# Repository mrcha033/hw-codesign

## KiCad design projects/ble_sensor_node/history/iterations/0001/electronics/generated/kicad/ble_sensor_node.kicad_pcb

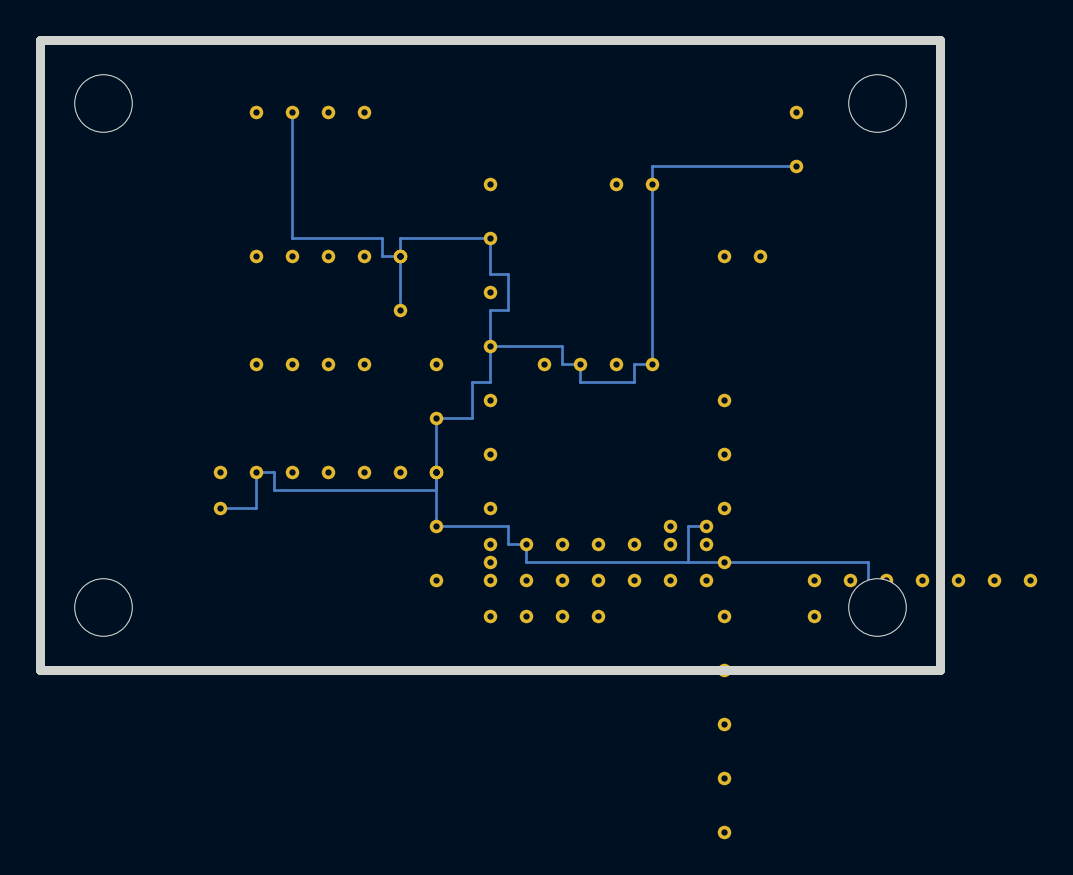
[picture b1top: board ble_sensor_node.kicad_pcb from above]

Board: 2 copper layers, 50.0 x 35.0 mm, 17 parts (0 on the bottom side), 21 nets.

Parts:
BT1: LiPo 400mAh; JST_PH_S2B-PH-K_1x02_P2.00mm_Horizontal
C1, C2: 100nF; C_0603_1608Metric
C3, C4: 10uF; C_1210_3225Metric
D1: USB ESD; SOT-23-6
J1: USB-C CHARGE; USB_C_GCT_USB4105
J2: SWD DEBUG; FTSH-105
LD1: 3V3 LDO; SOT-23-5
R1, R2: 4K7; R_0603_1608Metric
R3: 1K; R_0603_1608Metric
R4: 10K; R_0603_1608Metric
U1: nRF52840; nRF52840-QIAA
U2: LiPo Charger; SOT-23-8
U3: Fuel Gauge; VSON-9_2x3mm_P0.5mm
U5: Temp/Humidity; DFN-8-1EP_2x2.5mm_P0.5mm

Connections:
CHG_ISET: R4.1, U2.8
CHG_STAT: U1.7, U2.6
FUEL_ALRT: U1.9, U3.3
GND: BT1.2, C1.2, C2.2, C3.2, C4.2, D1.5, J1.2, J2.3, LD1.2, LD1.4, R4.2, U1.2, U2.2, U2.4, U3.4, U5.2, U5.7, U5.8
I2C_SCL: R1.2, U1.5, U3.2, U5.4
I2C_SDA: R2.2, U1.6, U3.1, U5.1
LED_BLE: R3.2, U1.10
NRST: J2.5, U1.11
SWDCLK: J2.4, U1.14
SWDIO: J2.2, U1.15
SWO: J2.6, U1.16
TEMP_INT: U1.8, U5.3
UART_RX: J2.8, U1.13
UART_TX: J2.7, U1.12
USB_DM: D1.4, U1.17
USB_DM_RAW: D1.3, J1.4
USB_DP: D1.2, U1.18
USB_DP_RAW: D1.1, J1.3
USB_VBUS: J1.1, U2.1
V3V3: C1.1, C2.1, C4.1, J2.1, LD1.1, LD1.5, R1.1, R2.1, R3.1, U1.1, U1.3, U1.4, U2.3, U2.7, U3.8, U5.5, U5.6
VBAT: BT1.1, C3.1, LD1.3, U2.5, U3.5, U3.6, U3.7, U3.9

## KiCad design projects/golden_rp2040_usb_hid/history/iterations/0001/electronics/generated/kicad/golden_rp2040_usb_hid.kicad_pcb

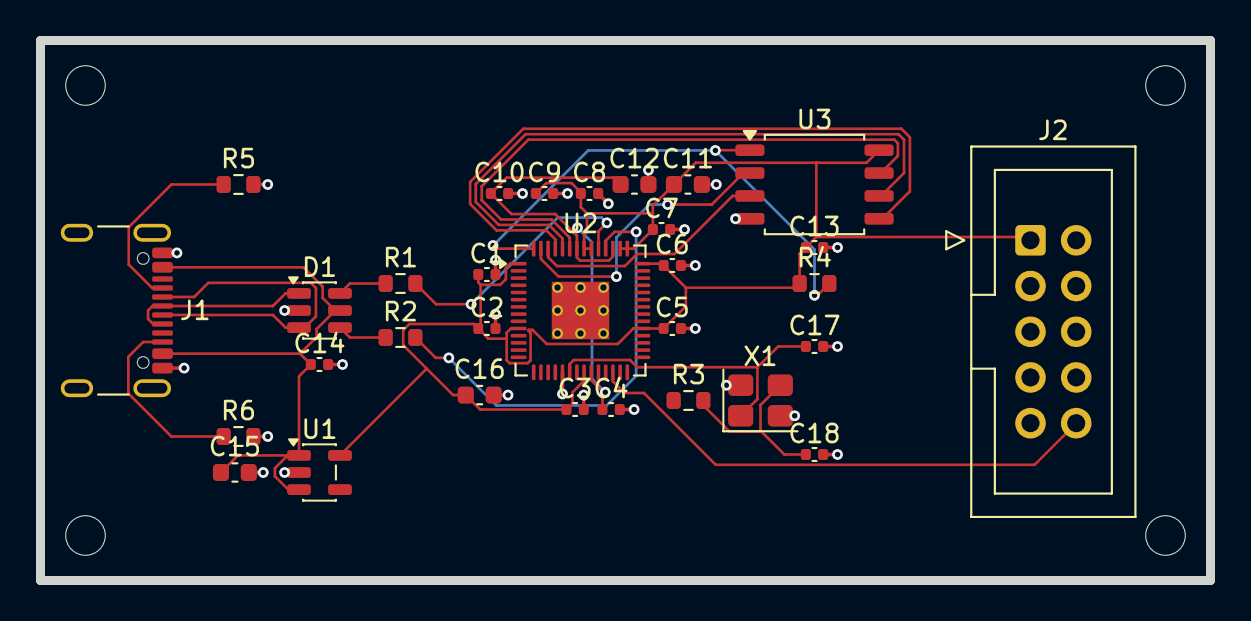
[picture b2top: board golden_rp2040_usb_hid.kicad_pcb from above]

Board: 2 copper layers, 65.0 x 30.0 mm, 35 parts (0 on the bottom side), 24 nets.

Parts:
C1, C2, C3, C4, C5, C6, C7, C8, C9, C10: 100nF; C_0402_1005Metric
C11: 1uF VREG_VIN; C_0603_1608Metric
C12: 1uF VREG_VOUT; C_0603_1608Metric
C13: 100nF FLASH; C_0402_1005Metric
C14: 100nF USB ESD VBUS; C_0402_1005Metric
C15: 1uF LDO input; C_0603_1608Metric
C16: 1uF LDO output; C_0603_1608Metric
C17, C18: 15pF XTAL; C_0402_1005Metric
D1: USB 2.0 ESD; SOT-23-6
H1, H2, H3, H4: MountingHole; MountingHole_2.2mm_Pad
J1: USB-C 2.0; USB_C_Receptacle_GCT_USB4105-xx-A_16P_TopMnt_Horizontal
J2: Cortex 10-pin SWD; IDC-Header_2x05_P2.54mm_Vertical
R1: 27R USB D+; R_0603_1608Metric
R2: 27R USB D-; R_0603_1608Metric
R3: 1K XTAL damping; R_0603_1608Metric
R4: 10K QSPI CS pull-up; R_0603_1608Metric
R5, R6: 5K1 USB-C Rd; R_0603_1608Metric
U1: 3V3 LDO; SOT-23-5
U2: RP2040; QFN-56-1EP_7x7mm_P0.4mm_EP3.2x3.2mm
U3: 16Mbit QSPI Flash; SOIC-8_5.3x5.3mm_P1.27mm
X1: 12MHz RP2040 crystal; Crystal_SMD_3225-4Pin_3.2x2.5mm

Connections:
GND: C1.2, C2.2, C3.2, C4.2, C5.2, C6.2, C7.2, C8.2, C9.2, C10.2, C11.2, C12.2, C13.2, C14.2, C15.2, C16.2, C17.2, C18.2, D1.2, J1.A1, J1.A12, J1.B1, J1.B12, J1.SH, J2.3, J2.5, J2.9, R5.2, R6.2, U1.2, U2.19, U2.57, U3.4, X1.2, X1.4
MCU_RUN: J2.10, U2.26
QSPI_CLK: U2.52, U3.6
QSPI_CS: R4.2, U2.56, U3.1
QSPI_D2: U2.54, U3.3
QSPI_D3: U2.51, U3.7
QSPI_MISO: U2.55, U3.2
QSPI_MOSI: U2.53, U3.5
SWCLK: J2.4, U2.24
SWDIO: J2.2, U2.25
USB_CC1: J1.A5, R5.1
USB_CC2: J1.B5, R6.1
USB_DM: R2.2, U2.46
USB_DM_ESD: D1.4, R2.1
USB_DM_RAW: D1.3, J1.A7, J1.B7
USB_DP: R1.2, U2.47
USB_DP_ESD: D1.6, R1.1
USB_DP_RAW: D1.1, J1.A6, J1.B6
USB_VBUS: C14.1, C15.1, D1.5, J1.A4, J1.A9, J1.B4, J1.B9, U1.1, U1.3
V1V1: C4.1, C10.1, C12.1, U2.23, U2.45, U2.50
V3V3: C1.1, C2.1, C3.1, C5.1, C6.1, C7.1, C8.1, C9.1, C11.1, C13.1, C16.1, J2.1, R4.1, U1.5, U2.1, U2.10, U2.22, U2.33, U2.42, U2.43, U2.44, U2.48, U2.49, U3.8
XIN: C17.1, U2.20, X1.1
XOUT: R3.1, U2.21
XTAL_RETURN: C18.1, R3.2, X1.3

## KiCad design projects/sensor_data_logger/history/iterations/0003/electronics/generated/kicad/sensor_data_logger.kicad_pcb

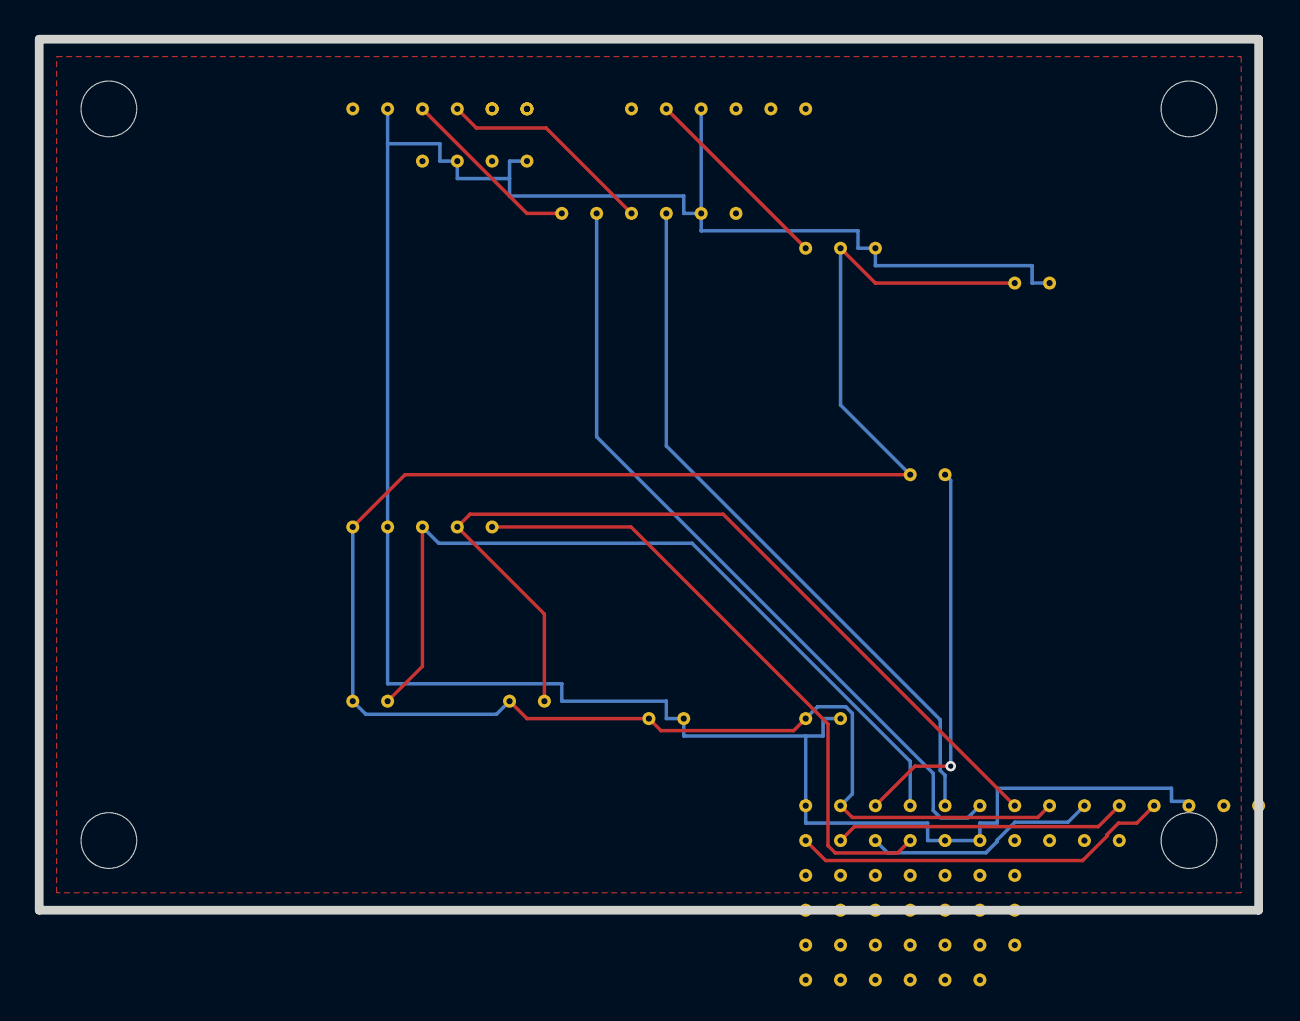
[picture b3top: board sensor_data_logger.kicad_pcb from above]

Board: 2 copper layers, 70.0 x 50.0 mm, 20 parts (0 on the bottom side), 18 nets.

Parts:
C1, C2: 100nF; C_0603_1608Metric
C9: 22uF; C_1206_3216Metric
D1: USB ESD; SOT-23-6
F1: 500mA Fuse; MIDI_Fuse
H1, H2, H3, H4: MountingHole; MountingHole_3.2mm_Pad
J1: USB-C POWER; USB_C_GCT_USB4105
J2: UART DEBUG; FTSH-105
Q1: Ideal Diode; SOT-23-6
R1, R2, R3: 4K7; R_0603_1608Metric
R5, R6: 5K1 USB-C Rd; R_0603_1608Metric
U1: ESP32-S3-WROOM-1
U2: ICM-42688-P; LGA-14
U3: 3V3 Buck; VQFN-16

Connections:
BOOT: J2.4, U1.27
ESP_EN: R3.2, U1.3
GND: C1.2, C2.2, C9.2, D1.5, J1.2, J2.5, Q1.3, R5.2, R6.2, U1.1, U1.40, U1.41, U2.2, U3.3
I2C_IMU_SCL: R1.2, U1.12, U2.3
I2C_IMU_SDA: R2.2, U1.15, U2.4
IMU_INT: U1.39, U2.5
UART_RX: J2.3, U1.36
UART_TX: J2.2, U1.37
USB_CC1: J1.5, R5.1
USB_CC2: J1.6, R6.1
USB_DM: D1.4, U1.13
USB_DM_RAW: D1.3, J1.4
USB_DP: D1.2, U1.14
USB_DP_RAW: D1.1, J1.3
USB_FUSED: F1.2, Q1.1
USB_PROT: Q1.2, U3.1
USB_VBUS: F1.1, J1.1
V3V3: C1.1, C2.1, C9.1, J2.1, R1.1, R2.1, R3.1, U1.2, U2.1, U3.2
